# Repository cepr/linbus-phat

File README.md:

# linbus-phat
LIN Bus interface for Raspberry PI Zero

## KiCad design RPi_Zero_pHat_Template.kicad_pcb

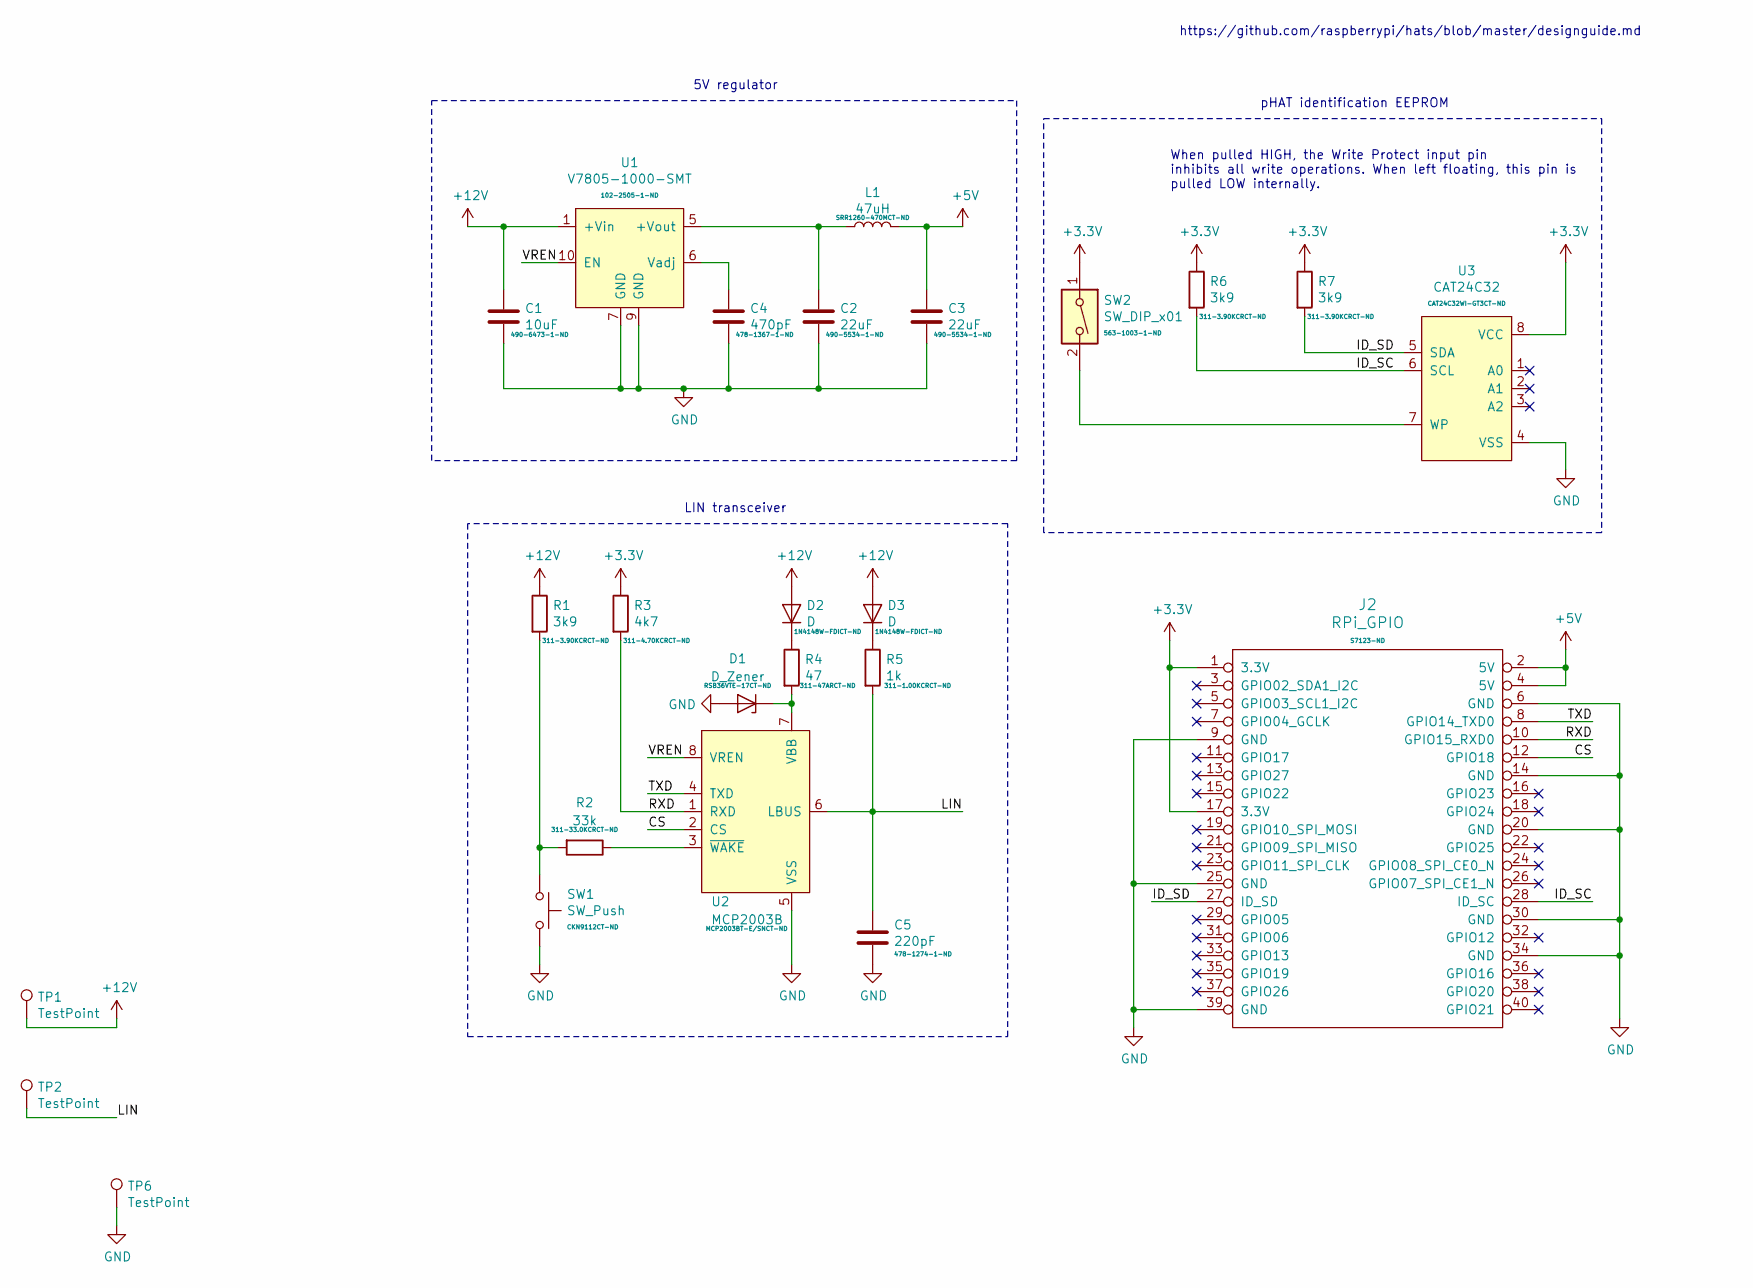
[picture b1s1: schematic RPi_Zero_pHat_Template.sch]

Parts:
C1: 10uF; C_0805; DIGIKEY 490-6473-1-ND
C2, C3: 22uF; C_0805; DIGIKEY 490-5534-1-ND
C4: 470pF; C_0805; DIGIKEY 478-1367-1-ND
C5: 220pF; C_0805; DIGIKEY 478-1274-1-ND
D1: D_Zener; D_SOD-323_HandSoldering; DIGIKEY RSB36VTE-17CT-ND
D2, D3: D; D_SOD-123; DIGIKEY 1N4148W-FDICT-ND
J2: RPi_GPIO; Pin_Header_Straight_2x20_Pitch2.54mm; DIGIKEY S7123-ND
L1: 47uH; BOURNS-SRR1260; DIGIKEY SRR1260-470MCT-ND
R1, R6, R7: 3k9; R_0805; DIGIKEY 311-3.90KCRCT-ND
R2: 33k; R_0805; DIGIKEY 311-33.0KCRCT-ND
R3: 4k7; R_0805; DIGIKEY 311-4.70KCRCT-ND
R4: 47; R_0805; DIGIKEY 311-47ARCT-ND
R5: 1k; R_0805; DIGIKEY 311-1.00KCRCT-ND
SW1: SW_Push; CK-PTS645; DIGIKEY CKN9112CT-ND
SW2: SW_DIP_x01; CHS-01TA; DIGIKEY 563-1003-1-ND
TP1, TP2, TP6: TestPoint; SolderWirePad_single_SMD_5x10mm
U1: V7805-1000-SMT; CUI-V78-1000-SMT; DIGIKEY 102-2505-1-ND
U2: MCP2003B; SOIC-8_3.9x4.9mm_Pitch1.27mm; DIGIKEY MCP2003BT-E/SNCT-ND
U3: CAT24C32; SOIC-8_3.9x4.9mm_Pitch1.27mm; DIGIKEY CAT24C32WI-GT3CT-ND

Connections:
+3V3: J2.1 (3.3V), J2.17 (3.3V), R3.1, R6.1, R7.1, SW2.1, U3.8 (VCC)
+5V: C3.1, J2.2 (5V), J2.4 (5V), L1.2
+12V: C1.1, D2.2 (A), D3.2 (A), R1.1, TP1.1, U1.1 (+Vin)
/CS: J2.12 (GPIO18), U2.2 (CS)
/ID_SC: J2.28 (ID_SC), R6.2, U3.6 (SCL)
/ID_SD: J2.27 (ID_SD), R7.2, U3.5 (SDA)
/LIN: C5.1, R5.2, TP2.1, U2.6 (LBUS)
/RXD: J2.10 (GPIO15_RXD0), R3.2, U2.1 (RXD)
/TXD: J2.8 (GPIO14_TXD0), U2.4 (TXD)
/VREN: U1.10 (EN), U2.8 (VREN)
GND: C1.2, C2.2, C3.2, C4.2, C5.2, D1.2 (A), J2.6 (GND), J2.9 (GND), J2.14 (GND), J2.20 (GND), J2.25 (GND), J2.30 (GND), J2.34 (GND), J2.39 (GND), SW1.2, TP6.1, U1.7 (GND), U1.9 (GND), U2.5 (VSS), U3.4 (VSS)
unnamed: C2.1, L1.1, U1.5 (+Vout)
unnamed: C4.1, U1.6 (Vadj)
unnamed: D1.1 (K), R4.2, U2.7 (VBB)
unnamed: D2.1 (K), R4.1
unnamed: D3.1 (K), R5.1
unnamed: R1.2, R2.2, SW1.1
unnamed: R2.1, U2.3 (~WAKE)
unnamed: SW2.2, U3.7 (WP)

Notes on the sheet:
When pulled HIGH, the Write Protect input pin inhibits all write operations. When left floating, this pin is pulled LOW internally.
https://github.com/raspberrypi/hats/blob/master/designguide.md
5V regulator
LIN transceiver
pHAT identification EEPROM

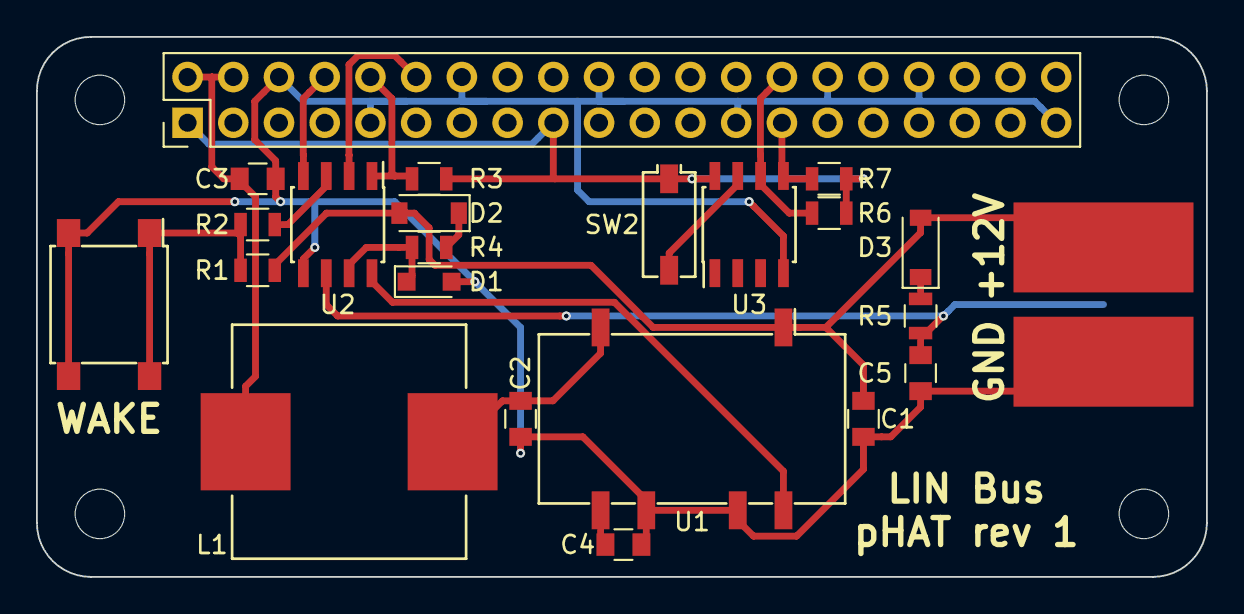
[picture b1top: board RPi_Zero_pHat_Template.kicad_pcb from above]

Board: 2 copper layers, 65.0 x 30.0 mm, 25 parts (1 on the bottom side), 19 nets.

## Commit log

2019-01-11 rev 1
